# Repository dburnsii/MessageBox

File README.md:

<!-- PROJECT SHIELDS -->
<!--
*** I'm using markdown "reference style" links for readability.
*** Reference links are enclosed in brackets [ ] instead of parentheses ( ).
*** See the bottom of this document for the declaration of the reference variables
*** for contributors-url, forks-url, etc. This is an optional, concise syntax you may use.
*** https://www.markdownguide.org/basic-syntax/#reference-style-links
-->
[![Contributors][contributors-shield]][contributors-url]
[![Forks][forks-shield]][forks-url]
[![Stargazers][stars-shield]][stars-url]
[![Issues][issues-shield]][issues-url]
[![MIT License][license-shield]][license-url]

<!-- PROJECT LOGO -->
<br />
<p align="center">
  <a href="https://github.com/dburnsii/MessageBox">
    <!-- Work in progress   -->
  </a>

  <h3 align="center">MessageBox</h3>

  <p align="center">
    Client-Side application for sharing heartfelt messages
    <br />
    <a href="https://github.com/dburnsii/MessageBox"><strong>Explore the docs »</strong></a>
    <br />
    <br />
    <a href="https://messagebox.unitfi.com">View Demo</a>
    ·
    <a href="https://github.com/dburnsii/MessageBox/issues">Report Bug</a>
    ·
    <a href="https://github.com/dburnsii/MessageBox/issues">Request Feature</a>
  </p>
</p>

<!-- TABLE OF CONTENTS -->
## Table of Contents

* [About the Project](#about-the-project)
  * [Built With](#built-with)
* [Getting Started](#getting-started)
  * [Prerequisites](#prerequisites)
  * [Installation](#installation)
* [Usage](#usage)
* [Roadmap](#roadmap)
* [Contributing](#contributing)
* [License](#license)
* [Contact](#contact)
* [Acknowledgements](#acknowledgements)

<!-- ABOUT THE PROJECT -->
## About The Project

This project serves as the client application for the MessageBox project. MessageBox allows you to easily
send messages to friends or loved ones with a simple and easy to use interface. The messages are
sent to the MessageBox hardware, and the user on the other end is notified of the new message. After
opening the box and reading the message, the box clears it's screen and listens for more messages.
This provides a clean interface to send personal messages to someone at work or home, without distracting
the recipient or requiring them to use any complex technology.

### Built With

* [PlatformIO](https://platformio.org/)

<!-- GETTING STARTED -->
## Getting Started

To get a MessageBox up and running follow these steps.

### Prerequisites

#### Hardware

You'll need the following:
* 3D Printed Parts in the `CAD_Files/FreeCAD` folder
* PCB in the `CAD_Files/KiCad` folder
* Off-the-shelf parts listed in `BOM.md`
* Soldering Iron and Solder
* (*Optional*)  Heatshrink Tubing
* (*Optional*)  Hot Glue Gun

#### Software

You'll need the following:
* PlatformIO

### Installation

1. To run the project, build and upload with PlatformIO:
```sh
pio run
pio run -t uploadfs
pio run -t upload
```

The uploadfs command will ensure all necessary SSL certificates are installed on the system, for use with HTTPS.

<!-- USAGE EXAMPLES -->
## Usage

Setup instructions will appear on the TFT LCD attached to the box.

<!-- ROADMAP -->
## Roadmap

See the [open issues](https://github.com/dburnsii/MessageBox/issues) for a list of proposed features (and known issues).

<!-- CONTRIBUTING -->
## Contributing

Contributions are what make the open source community such an amazing place to be learn, inspire, and create. Any contributions you make are **greatly appreciated**.

1. Fork the Project
2. Create your Feature Branch (`git checkout -b feature/AmazingFeature`)
3. Commit your Changes (`git commit -m 'Add some AmazingFeature'`)
4. Push to the Branch (`git push origin feature/AmazingFeature`)
5. Open a Pull Request

<!-- LICENSE -->
## License

Distributed under the MIT License. See `LICENSE` for more information.

<!-- CONTACT -->
## Contact

Desone Burns II - dburnsii@live.com

Project Link: [https://github.com/dburnsii/MessageBox](https://github.com/dburnsii/MessageBox)

<!-- ACKNOWLEDGEMENTS
## Acknowledgements

* 
* 
* 

-->

<!-- MARKDOWN LINKS & IMAGES -->
<!-- https://www.markdownguide.org/basic-syntax/#reference-style-links -->
[contributors-shield]: https://img.shields.io/github/contributors/dburnsii/MessageBox.svg?style=flat-square
[contributors-url]: https://github.com/dburnsii/MessageBox/graphs/contributors
[forks-shield]: https://img.shields.io/github/forks/dburnsii/MessageBox.svg?style=flat-square
[forks-url]: https://github.com/dburnsii/MessageBox/network/members
[stars-shield]: https://img.shields.io/github/stars/dburnsii/MessageBox.svg?style=flat-square
[stars-url]: https://github.com/dburnsii/MessageBox/stargazers
[issues-shield]: https://img.shields.io/github/issues/dburnsii/MessageBox.svg?style=flat-square
[issues-url]: https://github.com/dburnsii/MessageBox/issues
[license-shield]: https://img.shields.io/github/license/dburnsii/MessageBox.svg?style=flat-square
[license-url]: https://github.com/dburnsii/MessageBox/blob/master/LICENSE
[product-screenshot]: public/images/screenshot.png

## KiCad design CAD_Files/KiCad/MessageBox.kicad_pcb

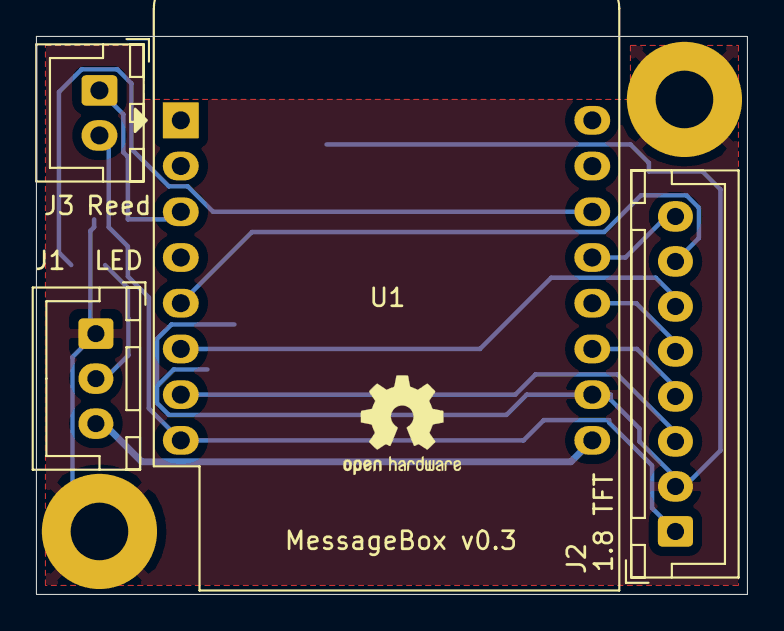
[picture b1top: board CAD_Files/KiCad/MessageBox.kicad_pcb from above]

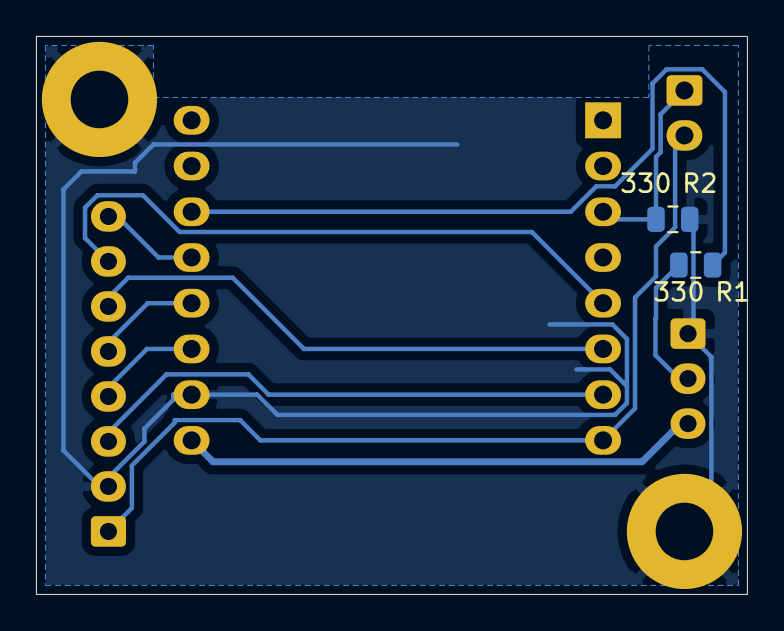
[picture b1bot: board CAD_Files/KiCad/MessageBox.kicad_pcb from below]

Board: 2 copper layers, 39.5 x 31.0 mm, 6 parts (2 on the bottom side), 12 nets.

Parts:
J1: Conn_01x03_Female; JST_XH_B3B-XH-A_1x03_P2.50mm_Vertical
J2: 1.8 TFT; JST_XH_B8B-XH-A_1x08_P2.50mm_Vertical
J3: Reed Switch; JST_XH_B2B-XH-A_1x02_P2.50mm_Vertical
R1, R2: 330; R_0805_2012Metric
U1: WeMos_D1_mini; WEMOS_D1_mini_light

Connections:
+3V3: J2.1, J3.2, U1.8
+5V: J1.3, U1.9
GND: J1.1, J2.2, R2.1, U1.10
unnamed: J1.2, R1.1
unnamed: J2.3, U1.7
unnamed: J2.4, U1.11
unnamed: J2.5, U1.12
unnamed: J2.6, U1.6
unnamed: J2.7, U1.5
unnamed: J2.8, U1.13
unnamed: J3.1, R2.2, U1.3
unnamed: R1.2, U1.14

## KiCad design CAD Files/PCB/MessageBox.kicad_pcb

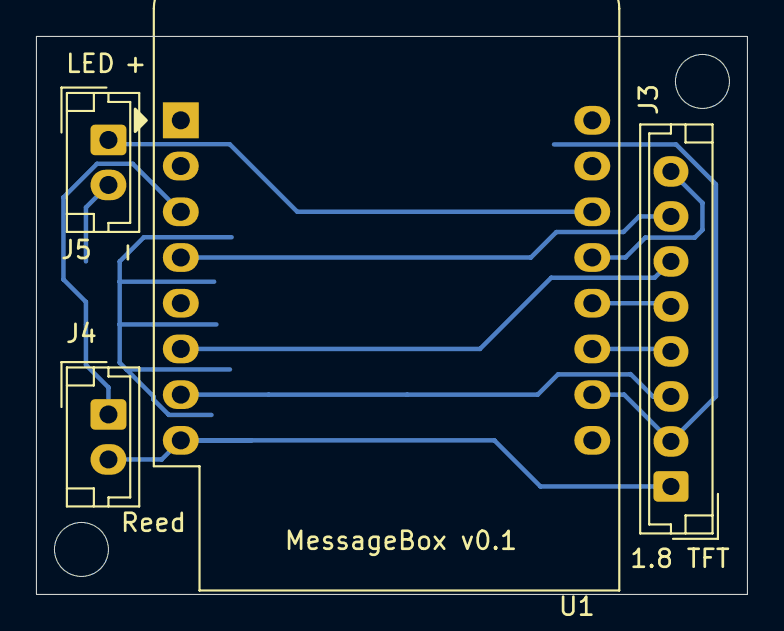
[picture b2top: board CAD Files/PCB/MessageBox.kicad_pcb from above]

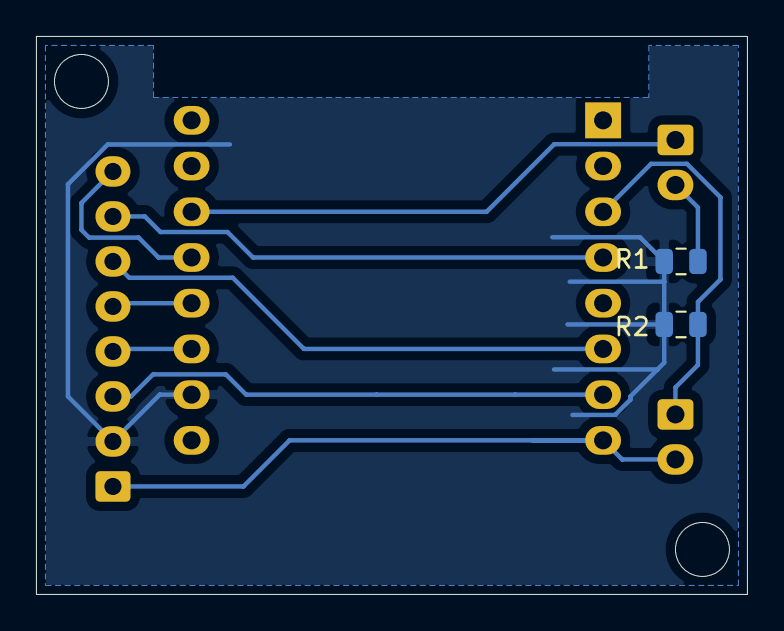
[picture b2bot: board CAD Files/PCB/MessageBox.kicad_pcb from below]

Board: 2 copper layers, 39.5 x 31.0 mm, 6 parts (2 on the bottom side), 11 nets.

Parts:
J3: 1.8 TFT; JST_EH_B8B-EH-A_1x08_P2.50mm_Vertical
J4: Reed Switch; JST_EH_B2B-EH-A_1x02_P2.50mm_Vertical
J5: LED; JST_EH_B2B-EH-A_1x02_P2.50mm_Vertical
R1, R2: R_US; R_0805_2012Metric
U1: WeMos_D1_mini; WEMOS_D1_mini_light

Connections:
+3V3: J3.1, J4.2, U1.8
GND: J3.2, R1.1, R2.1, U1.10
unnamed: J3.3, U1.7
unnamed: J3.4, U1.11
unnamed: J3.5, U1.12
unnamed: J3.6, U1.6
unnamed: J3.7, U1.4
unnamed: J3.8, U1.13
unnamed: J4.1, R2.2, U1.3
unnamed: J5.1, U1.14
unnamed: J5.2, R1.2

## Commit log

2020-06-11 Initial functionality
2020-06-15 Shows message on screen with lid sensor
2020-07-16 Added BOM, Updated to ST7735
2020-07-16 Added Initial CAD File
2020-07-24 Change to image transfer
2020-08-08 Create LICENSE
2020-08-08 Added PCBs, switch to images
2020-10-25 Update code, update CAD files
2020-10-30 Switch to PlatformIO
2020-10-30 Update README and fix http refresh
2020-11-02 Update build steps
2020-11-02 Update BOM and Readme
2021-10-19 Add github actions
2021-10-19 Updates for CI build
2021-10-19 Temporarily downgrade the platform to resolve build issues
2021-10-19 Only upload the actual firmware
2021-11-19 Enable OTA and local http testing
2021-11-23 Updated board, fixes for build, added debug logic
